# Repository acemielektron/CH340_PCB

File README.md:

# CH340_PCB
diy single sided CH340 based 3.3v usb serial pcb

All pins of ch340g are routed on a very small single sided diy pcb

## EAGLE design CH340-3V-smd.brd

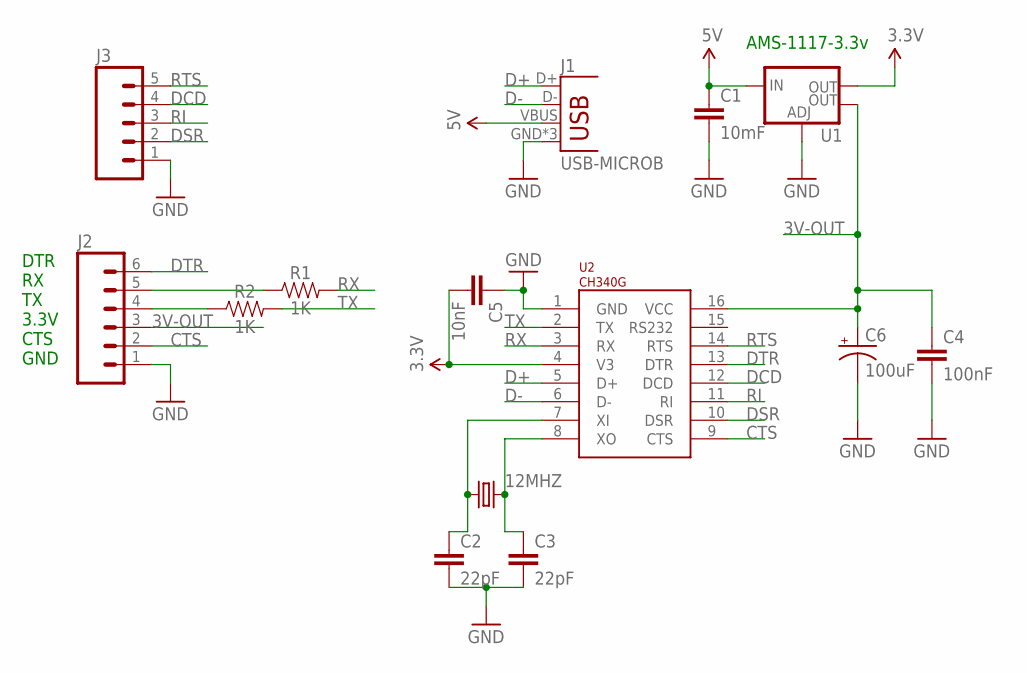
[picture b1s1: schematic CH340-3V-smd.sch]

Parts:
12MHZ: CRYSTALHC49US; HC49US
C1: 10mF; 0805
C2, C3: 22pF; 1206
C4: 100nF; 1206
C5: 10nF; 1206
C6: 100uF; EIA3528
J1: USB-MICROB
J2: M06SILK_FEMALE_PTH; 1X06
J3: M05PTH; 1X05
R1, R2: 1K; 0805
U1: V_REG_LM1117SOT223; SOT223
U2: CH340G; SOIC16

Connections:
3.3V: C5.2, U1.2 (OUT), U2.4 (V3)
3V-OUT: C4.1, C6.A (+), J2.3, U1.4 (OUT), U2.16 (VCC)
5V: C1.1, J1.VBUS, U1.3 (IN)
CTS: J2.2, U2.9 (CTS)
D+: J1.D+, U2.5 (D+)
D-: J1.D-, U2.6 (D-)
DCD: J3.4, U2.12 (DCD)
DSR: J3.2, U2.10 (DSR)
DTR: J2.6, U2.13 (DTR)
GND: C1.2, C2.2, C3.2, C4.2, C5.1, C6.C (-), J1.GND, J1.MT1 (GND), J1.MT2 (GND), J2.1, J3.1, U1.1 (ADJ), U2.1 (GND)
unnamed: 12MHZ.1, C2.1, U2.7 (XI)
unnamed: 12MHZ.2, C3.1, U2.8 (XO)
unnamed: J2.5, R1.1
unnamed: J2.4, R2.1
RI: J3.3, U2.11 (RI)
RTS: J3.5, U2.14 (RTS)
RX: R1.2, U2.3 (RX)
TX: R2.2, U2.2 (TX)

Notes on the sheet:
DTR RX TX 3.3V CTS GND
AMS-1117-3.3v

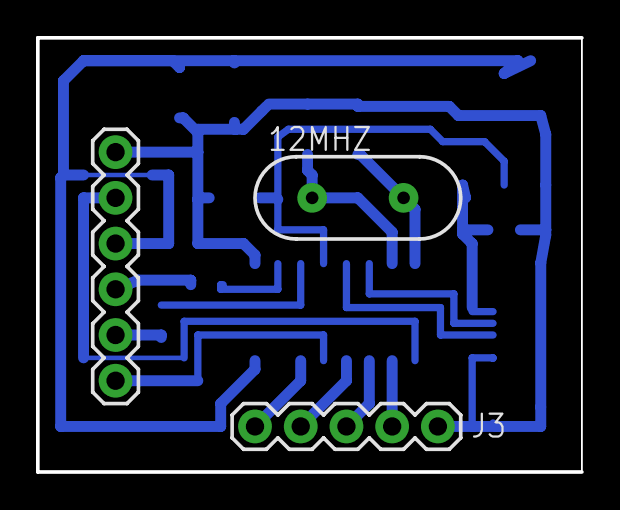
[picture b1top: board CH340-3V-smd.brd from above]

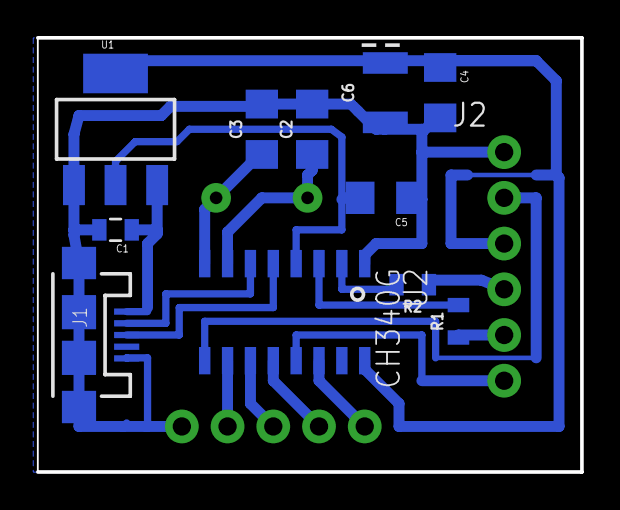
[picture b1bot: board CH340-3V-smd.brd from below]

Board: 2 copper layers, 30.2 x 24.1 mm, 14 parts (11 on the bottom side), 18 nets.

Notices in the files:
parts and their libraries:
SparkFun-Capacitors: Licensing: Creative Commons ShareAlike 4.0 International - https://creativecommons.org/licenses/by-sa/4.0
